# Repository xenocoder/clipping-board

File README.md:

Daughterboard to allow clipping options.

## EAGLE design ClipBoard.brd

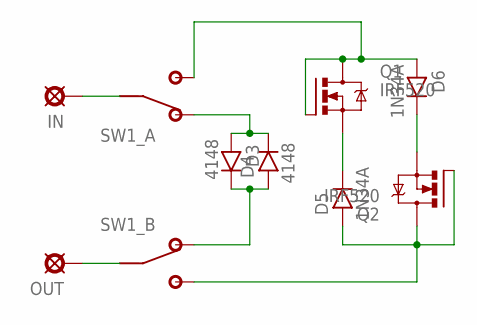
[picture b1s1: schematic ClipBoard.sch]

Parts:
D3, D4: 4148; DO35-3
D5, D6: 1N34A; DO07
IN: CLIPIN; SQUARE
OUT: CLIPOUT; SQUARE
Q1, Q2: IRF520; TO220BV
SW1: DPDT; DPDT_PCB

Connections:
unnamed: D3.C, D4.A, SW1.B2 (1)
unnamed: D5.C, Q1.S
unnamed: OUT.1, SW1.B1 (2)
unnamed: D6.C, Q2.S
unnamed: D6.A, Q1.D, Q1.G, SW1.A3 (3)
unnamed: IN.1, SW1.A1 (2)
unnamed: D3.A, D4.C, SW1.A2 (1)
unnamed: D5.A, Q2.D, Q2.G, SW1.B3 (3)

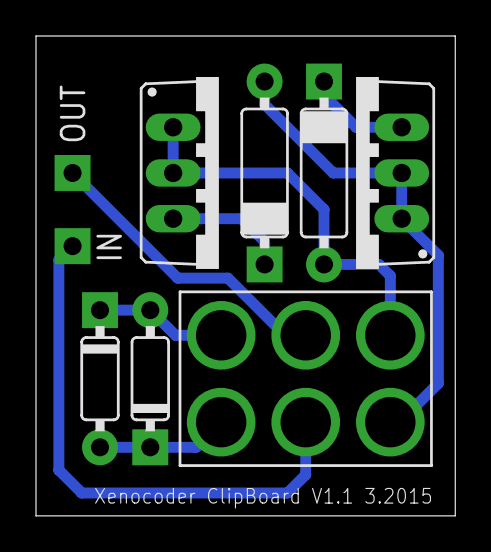
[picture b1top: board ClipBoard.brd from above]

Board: 2 copper layers, 23.3 x 26.7 mm, 9 parts (0 on the bottom side), 8 nets.

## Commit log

2015-10-08 Added files for v1.0
2015-10-08 Changes to board and schematic to make v1.1
